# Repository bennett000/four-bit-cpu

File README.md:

Four Bit CPU
============

Ever wonder how a CPU works? Do you want to learn the answers the hard way?

If so this is the repository for you.

## The Goal

Build a "macroprocessor" turing machine that can execute an assembly language.

How hard could it be?

## Inspirations

* [Simple CPU](https://www-users.cs.york.ac.uk/~mjf/simple_cpu/index.html "Simple CPU with FPGA"), on which this project is _heavily_ based.  Thanks [Mike](mike.freeman@york.ac.uk "Mike Freeman, York")
* [Mega Processor](http://www.megaprocessor.com/ "The Mega Processor"), cemented the desire to stick to four bits.  Also had great retrospectives that highlighted the strenghts of Mike Freeman's emphasis on "Clock Enable" circuitry
* [All About Circuits](https://www.allaboutcircuits.com/textbook/ "All About Circuits Electronic Textbook") wonderful text for explaining the fundamentals of electricity and electronics

## Assumed Knowledge

It will be challenging to list all the assumed knowledge here. We've been fiddling with software for decades, but electronics not so much.

* Knowledge of some form of computer programming.  Assembly would be nice but the concepts of a higher level language like Python or JavaScript are very transferrable
* Basic knowledge of electricity, think simple pipe analogy, but not much knowledge of semi-conductors
* Basic knowledge of discrete mathematics, think truth tables, but not necessarily how to do algebra with discrete math (although that helps)

## License

* Any software written for this project is subject to [GPLv3](./LICENSE)
* All documentation is subject to the [Creative Commons Attribution-NonCommercial-ShareAlike 4.0 International](https://creativecommons.org/licenses/by-nc-sa/4.0/legalcode) license terms

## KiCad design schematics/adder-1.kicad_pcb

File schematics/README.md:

4-bit-cpu Schematics
====================

This folder is a series of KiCad projects, it might be possible to nest the folders and clean up the structure.  For now all the files are in the folder with no structure.  There is a file name convention.  There are also some utilities for testing projects using SPICE.

## Requirements

* KiCad 5.x
* ngspice
* nodejs 8+

## Naming Convention

Due to having _many_ files in one folder the naming convention is important.

* Names use the format `[thing]-[bits]-[inputs]-[outputs]` (`outputs` is optional and mostly used for multiplexers) (there are some errors to this convention as I've found :( )
* The `-test` extension indicates that the project or worksheet is a test harness.  These files _consume_ sheets (and sometimes projects) and can be thought of as "unit test" or in the higher order cases "integration tests".  To be automated, these tests *must* have a power supply for each input you'd like to test
* The files starting with `four-bit-cpu*` are legacy and will be refactored
* I/O names on KiCad sheets use one (`1`) based indexing
* KiCad names use `ALL CAPS` for acronyms and `CamelCase` for short forms

## SPICE Conventions

* Casing matters.  Even though it doesn't matter to SPICE it matters to some of the tooling

## Utilities

`test.js` is a utility for running tests automatically or manually.  The tool is currently evolving.  The tool:

* Reads in `*.cir` files based on CLI arguments
* _In memory_ the script modifies the `*.cir` as per the values in that `*.cir`'s corresponding JSON test file (format is described below)
* The script then runs an `.op` analysis for each truth table specified in the test JSON.
* The script outputs either raw `ngspice` output _or_ a summary of the tests

### Usage

`./schematics/test.js alu` would cause the script to look for `./schematics/alu-test.cir`, _and_ `./schematics/test/alu.json`.  The script would then run `ngspice` once for each test specified in [alu.json](./schematics/test/alu.json "ALU Tests")

The output would look something like:

```bash
[ { '/alu/cout': '✓',
    '/alu/z4': '✓',
    '/alu/z3': '✓',
    '/alu/z2': '✓',
    '/alu/z1': '✓' },
  { '/alu/cout': '✓',
    '/alu/z4': '✓',
    '/alu/z3': '✓',
    '/alu/z2': '✓',
    '/alu/z1': '✓' },
    ...
    (Output hidden, there are lots of tests)
    ...
]
```

Sometimes it's useful to get the actual output of `ngspice` this can be done with a similar command:

`./schematics/test.js run alu`, this would dump the raw `ngspice` output _for each test_.  Redirecting `stdout` to a file is recommended.  Example: `./schematics/test.js run alu > output`.  Then use an editor or `cat output | grep` to search the output.

### Test Data

Data for automatic testing is stored in `schematics/tests` the format is JSON and looks like so:

```json
{
  "tests": [{
    "i": { "/Ain": 0, "/Bin": 0, "/Cin": 0 },
    "o": { "/nor-3/q": 1 } 
    },{
    "i": { "/Ain": 1, "/Bin": 1, "/Cin": 0 },
    "o": { "/nor-3/q": 0 } 
    },]
}
```

The above format is taken from [nor-3](./schematics/tests/gate-nor-3.json "nor-3 truth table tests")

* The `tests` array has a list of objects
* Each object in the test array has an `i` (input), and an `o` output property.
* The input/output properties are dictionaries of a particular circuits input values and their expected outputs.

In the above example, if `Ain`, `Bin`, and `Cin` are all `0` we can expect the output `nor-3/q` to be `1`, which makes sense.  None of the inputs are in a HIGH state and that satisfies nor.

## License

* Any software written for this project is subject to [GPLv3](../LICENSE)
* All documentation is subject to the [Creative Commons Attribution-NonCommercial-ShareAlike 4.0 International](https://creativecommons.org/licenses/by-nc-sa/4.0/legalcode) license terms

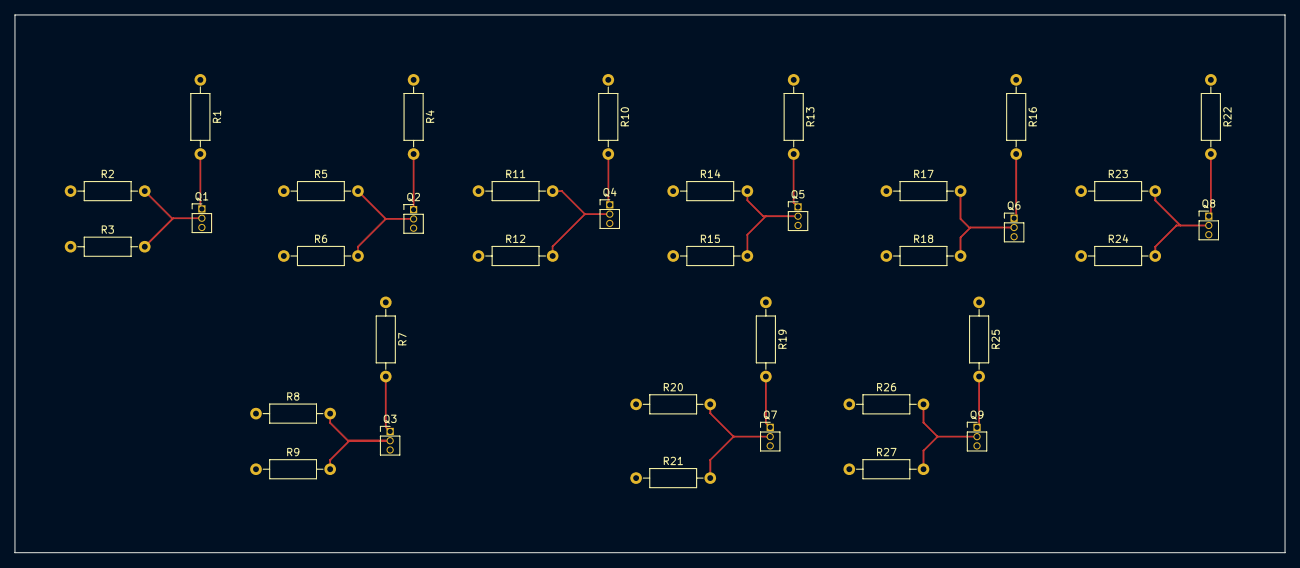
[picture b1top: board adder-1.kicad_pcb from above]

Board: 2 copper layers, 174.0 x 73.7 mm, 36 parts (0 on the bottom side), 23 nets.

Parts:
Q1, Q2, Q3, Q4, Q5, Q6, Q7, Q8, Q9: NPN; Socket_Strip_Straight_1x03_Pitch1.27mm
R1, R4, R7, R10, R13, R16, R19, R22, R25: 1K; R_Axial_DIN0207_L6.3mm_D2.5mm_P10.16mm_Horizontal
R2, R3, R5, R6, R8, R9, R11, R12, R14, R15, R17, R18, R20, R21, R23, R24, R26, R27: 10K; R_Axial_DIN0207_L6.3mm_D2.5mm_P10.16mm_Horizontal

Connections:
/A: R2.1, R5.1
/B: R3.1, R9.1
/Cin: R15.1, R21.1
/Cout: Q9.1, R25.2
/Gnd: Q1.3, Q2.3, Q3.3, Q4.3, Q5.3, Q6.3, Q7.3, Q8.3, Q9.3
/S: Q8.1, R22.2
/Vcc: R1.1, R4.1, R7.1, R10.1, R13.1, R16.1, R19.1, R22.1, R25.1
/adder-1-nor-1/AorB: Q1.2, R2.2, R3.2
/adder-1-nor-2/AorB: Q2.2, R5.2, R6.2
/adder-1-nor-3/A: Q1.1, R1.2, R6.1, R8.1, R27.1
/adder-1-nor-3/AorB: Q3.2, R8.2, R9.2
/adder-1-nor-4/A: Q2.1, R4.2, R11.1
/adder-1-nor-4/AorB: Q4.2, R11.2, R12.2
/adder-1-nor-4/B: Q3.1, R7.2, R12.1
/adder-1-nor-5/A: Q4.1, R10.2, R14.1, R17.1
/adder-1-nor-5/AorB: Q5.2, R14.2, R15.2
/adder-1-nor-6/AorB: Q6.2, R17.2, R18.2
/adder-1-nor-7/A: Q5.1, R13.2, R18.1, R20.1, R26.1
/adder-1-nor-7/AorB: Q7.2, R20.2, R21.2
/adder-1-nor-8/AorB: Q9.2, R26.2, R27.2
/adder-1-nor-9/A: Q6.1, R16.2, R23.1
/adder-1-nor-9/AorB: Q8.2, R23.2, R24.2
/adder-1-nor-9/B: Q7.1, R19.2, R24.1

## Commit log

2019-01-17 Building a CPU from resistor transistor logic
2019-01-19 Fleshes out basic schematics and some utility software
2019-01-19 Adds a test for the 4-4-1 multiplexer
2019-01-19 Adds an xor gate
2019-01-19 Updates gitignore to include common swap files and data output
2019-01-19 Adds a four bit bitwise inverter
2019-01-19 Adds a one bit buffer
2019-01-19 Adds a 1->4 bit replicator
2019-01-19 squash
2019-01-19 Adds a 4 bit and gate
2019-01-20 ALU is sketched but has functional defects
2019-01-20 Adds a netlist "optimizer" which shortens names for better output parsing
2019-01-20 Adds a simple spice runner
2019-01-20 Adds a model injector and an op test injector
2019-01-20 Basic unit test automation framework for async circuits
2019-01-20 Adds a primitive directory iterator
2019-01-21 Adds some tests for and-2, nor-2, nor-3
2019-01-22 Test output is a bit more functional... ALU still has defects
2019-01-26 More testing. Trying to find defect in ALU
2019-02-02 ALU appears to work as expected
2019-02-02 Updates README, adds some ALU tests
2019-02-02 Updates the schematics' README
2019-02-02 Adds ALU Schematics (#1)
    * Adds a test for the 4-4-1 multiplexer
    * Adds an xor gate
    * Updates gitignore to include common swap files and data output
    * Adds a four bit bitwise inverter
    * Adds a one bit buffer
    * Adds a 1->4 bit replicator
2019-02-05 WIP - flip-flop-d-pre
2019-02-17 Can now automate transient analysis
